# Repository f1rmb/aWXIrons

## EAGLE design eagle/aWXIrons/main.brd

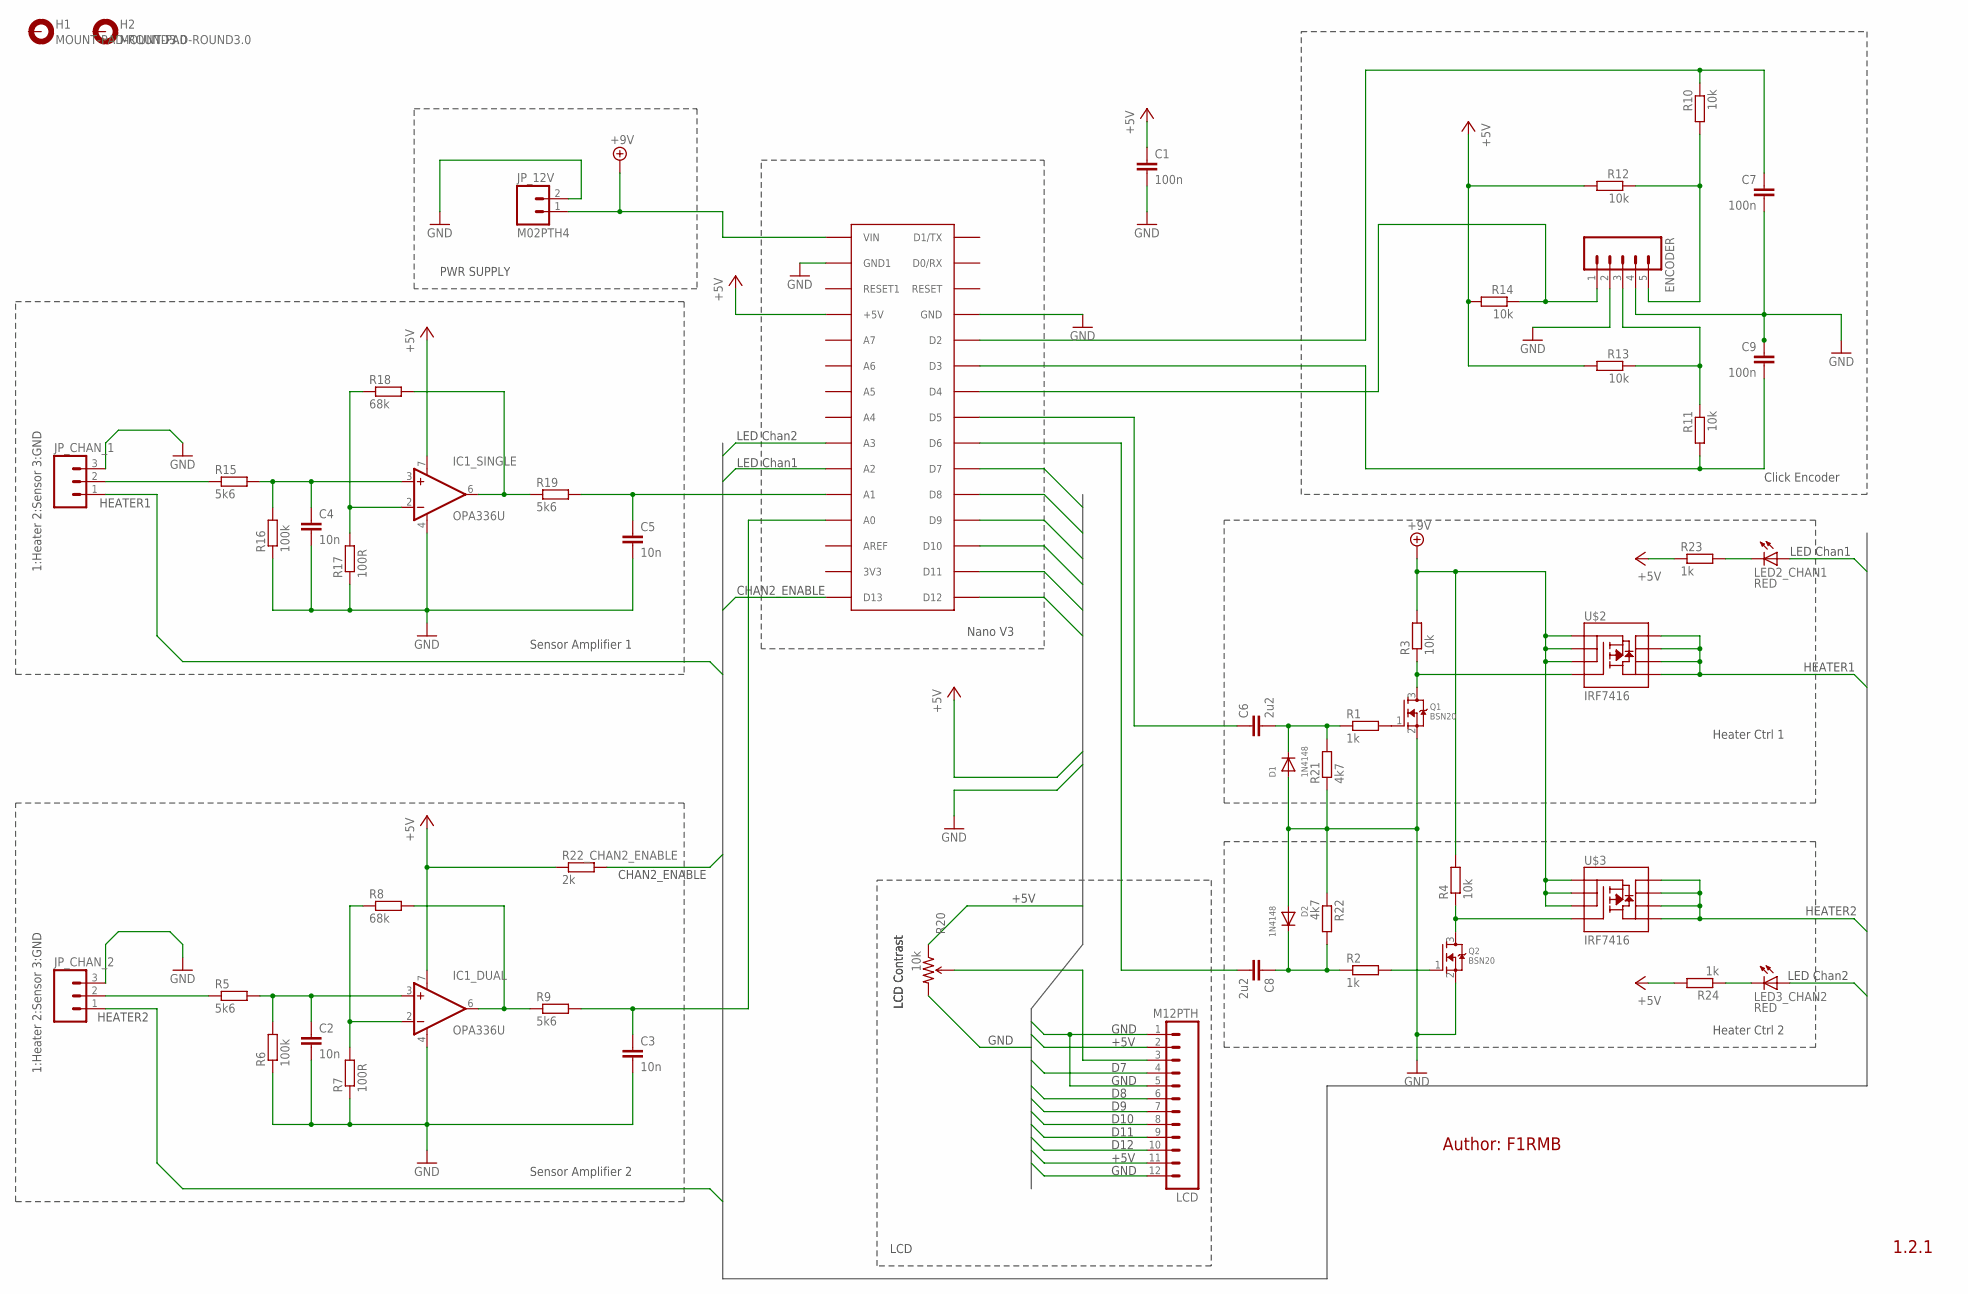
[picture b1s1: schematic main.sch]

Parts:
C1, C7, C9: 100n; C0805
C2, C3, C4, C5: 10n; C0805
C6, C8: 2u2; C0805
D1, D2: 1N4148; SOD-123
ENCODER: M05PTH; 1X05
H1, H2: MOUNT-PAD-ROUND3.0; 3,0-PAD
IC1_DUAL, IC1_SINGLE: OPA336U; SO08
JP_12V: M02PTH4; 1X02_XTRA_BIG
JP_CHAN_1, JP_CHAN_2: M03SCREW; SCREWTERMINAL-3.5MM-3
LCD: M12PTH; 1X12
LED2_CHAN1, LED3_CHAN2: RED; LED3MM
Q1, Q2: BSN20; SOT23
R1, R2, R23, R24: 1k; R0805
R3, R4, R10, R11, R12, R13, R14: 10k; R0805
R5, R9, R15, R19: 5k6; R0805
R6, R16: 100k; R0805
R7, R17: 100R; R0805
R8, R18: 68k; R0805
R20: 10k; 3362U-2
R21, R22: 4k7; R0805
R22_CHAN2_ENABLE: 2k; R0805
U$1: ARDUINONANO; PDIP-32
U$2, U$3: IRF7416; SO08

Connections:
+5V: C1.1, IC1_DUAL.7 (V+), IC1_SINGLE.7 (V+), LCD.2, LCD.11, R12.2, R13.2, R14.2, R20.1 (CCW), R22_CHAN2_ENABLE.1, R23.1, R24.2, U$1.+5V
+9V: JP_12V.1, R3.2, R4.2, U$1.VIN, U$2.1 (S), U$2.2 (S), U$2.3 (S), U$3.1 (S), U$3.2 (S), U$3.3 (S)
DB4: LCD.7, U$1.D9
DB5: LCD.8, U$1.D10
DB6: LCD.9, U$1.D11
DB7: LCD.10, U$1.D12
E: LCD.6, U$1.D8
ENABLECHAN2: R22_CHAN2_ENABLE.2, U$1.D13
GND: C1.2, C2.2, C3.2, C4.2, C5.2, C7.2, C9.1, D1.A, D2.A, ENCODER.2, ENCODER.4, IC1_DUAL.4 (V-), IC1_SINGLE.4 (V-), JP_12V.2, JP_CHAN_1.3, JP_CHAN_2.3, LCD.1, LCD.5, LCD.12, Q1.2 (S), Q2.2 (S), R6.1, R7.1, R16.1, R17.1, R20.3 (CW), R21.1, R22.1, U$1.GND, U$1.GND1
HEATCHAN1: LED2_CHAN1.A, U$1.A2
HEATCHAN2: LED3_CHAN2.A, U$1.A3
HEATER1: JP_CHAN_1.1, U$2.5 (D), U$2.6 (D), U$2.7 (D), U$2.8 (D)
HEATER2: JP_CHAN_2.1, U$3.5 (D), U$3.6 (D), U$3.7 (D), U$3.8 (D)
unnamed: Q1.3 (D), R3.1, U$2.4 (G)
unnamed: Q2.3 (D), R4.1, U$3.4 (G)
unnamed: JP_CHAN_2.2, R5.1
unnamed: C2.1, IC1_DUAL.3 (+IN), R5.2, R6.2
unnamed: IC1_DUAL.2 (-IN), R7.2, R8.1
unnamed: C7.1, R10.1, U$1.D2
unnamed: IC1_DUAL.6 (OUT), R8.2, R9.1
unnamed: JP_CHAN_1.2, R15.1
unnamed: C4.1, IC1_SINGLE.3 (+IN), R15.2, R16.2
unnamed: C6.1, U$1.D5
unnamed: C8.2, U$1.D6
unnamed: Q1.1 (G), R1.2
unnamed: Q2.1 (G), R2.2
unnamed: C3.1, R9.2, U$1.A0
unnamed: ENCODER.5, R10.2, R12.1
unnamed: LCD.3, R20.2 (WIPER)
unnamed: C6.2, D1.C, R1.1, R21.2
unnamed: ENCODER.3, R11.1, R13.1
unnamed: C9.2, R11.2, U$1.D3
unnamed: IC1_SINGLE.2 (-IN), R17.2, R18.1
unnamed: IC1_SINGLE.6 (OUT), R18.2, R19.1
unnamed: ENCODER.1, R14.1, U$1.D4
unnamed: C5.1, R19.2, U$1.A1
unnamed: C8.1, D2.C, R2.1, R22.2
unnamed: LED2_CHAN1.K (C), R23.2
unnamed: LED3_CHAN2.K (C), R24.1
RS: LCD.4, U$1.D7

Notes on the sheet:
1:Heater 2:Sensor 3:GND
PWR SUPPLY
LCD
Nano V3
Click Encoder
Sensor Amplifier 1
Sensor Amplifier 2
Heater Ctrl 1
Heater Ctrl 2
LED Chan1
LED Chan2
LCD Contrast
1.2.1
Author: F1RMB
CHAN2_ENABLE
+5V
GND
D10
D11
D12
HEATER1
HEATER2

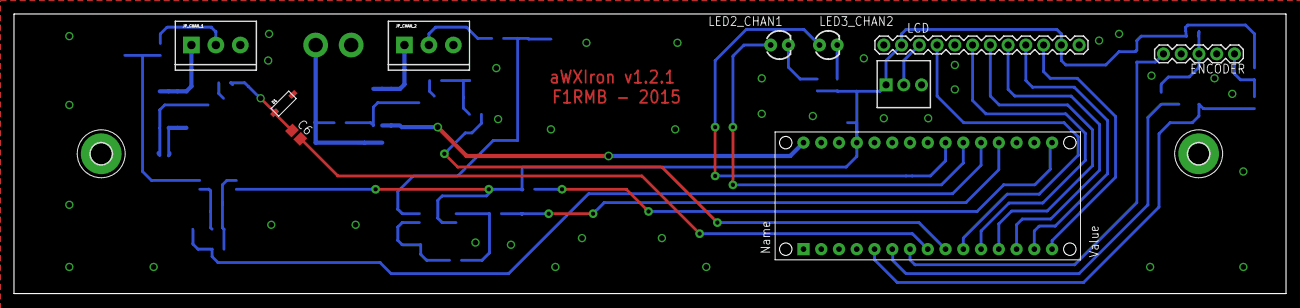
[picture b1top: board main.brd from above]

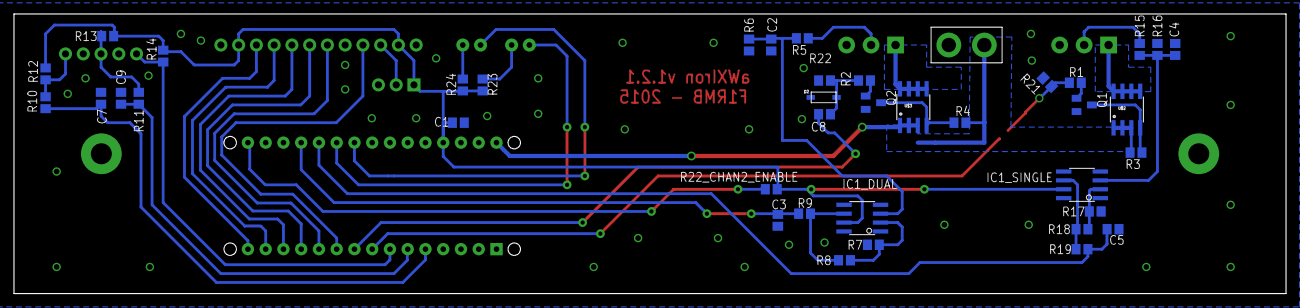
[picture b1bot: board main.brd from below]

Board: 2 copper layers, 182.0 x 40.0 mm, 52 parts (40 on the bottom side), 40 nets.

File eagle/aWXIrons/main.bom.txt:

Partlist exported from /home/daniel/eagle/Projects/aWXIrons/main.sch at 11/04/15 07:46

Assembly variant: 

Qty Value              Device                     Parts                          
2                      M03SCREW                   JP_CHAN_1, JP_CHAN_2           
1                      M05PTH                     ENCODER                        
2   1N4148             DIODESOD-123               D1, D2                         
4   1k                 R-EU_R0805                 R1, R2, R23, R24               
1   2k                 R-EU_R0805                 R22_CHAN2_ENABLE               
2   2u2                C-EUC0805                  C6, C8                         
2   4k7                R-EU_R0805                 R21, R22                       
4   5k6                R-EU_R0805                 R5, R9, R15, R19               
7   10k                R-EU_R0805                 R3, R4, R10, R11, R12, R13, R14
1   10k                TRIMPOT3362U-2             R20                            
4   10n                C-EUC0805                  C2, C3, C4, C5                 
2   68k                R-EU_R0805                 R8, R18                        
2   100R               R-EU_R0805                 R7, R17                        
2   100k               R-EU_R0805                 R6, R16                        
3   100n               C-EUC0805                  C1, C7, C9                     
1   ARDUINONANO        ARDUINONANO                U$1                            
2   BSN20              MOSFET-NREFLOW             Q1, Q2                         
2   IRF7416            MOSFET-PCHANNEL-SOIC8SOIC8 U$2, U$3                       
1   M02PTH4            M02PTH4                    JP_12V                         
1   M12PTH             M12PTH                     LCD                            
2   MOUNT-PAD-ROUND3.0 MOUNT-PAD-ROUND3.0         H1, H2                         
2   OPA336U            OPA336U                    IC1_DUAL, IC1_SINGLE           
2   RED                LED3MM                     LED2_CHAN1, LED3_CHAN2

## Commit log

2015-03-29 First Import.
2015-03-31 Finalize Makefile. Update doc (unfinished). Turn both channels PWM off while reading ADC. Add plugged tip detection (display shows '---' when unplugged). In joined channels mode, temperature display 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
2015-04-05 Finalize documentation. Fix calibration process.
2015-04-05 Added tag RELEASE-1.2_02042015 for changeset efbd99d3a2c3
2015-04-05 Prepare to publish on GitHub.
2015-04-11 Update PDFs
2015-04-13 - Displayed temperature is averaged. - Fix documentation (F6AZZ). - Bump version, update user manual.
2015-04-13 Revert "- Displayed temperature is averaged."
    This reverts commit 4ef88245852de1e1e4a668eb0dcc3ed734a76e18.
2015-04-13 - Displayed temperature is now averaged. - Fix documentation (F6AZZ). - Bump version, update user manual. - New release.
2015-04-13 Change +12V to +9V in schematic and PCBs. Update PDFs.
2015-04-13 Update doc version.
2016-03-10 Fix small if statement error (not critical). Bump version number. New HEX file.
2017-01-29 Fix averaging class, stupid me... Bump version.
2017-01-29 :CAL:DUMP displays EEPROM calibration values. Update copyright year. More cleanup.
2017-01-30 Reintroduce averaging made of double values. Use and fix usage of strcmp_P and snprintf_P. Update doc. Release.
2017-01-30 Forgot the HEX file...
2017-08-21 Make it compile on 'standard' arduino install (in /opt/arduino).

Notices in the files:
parts and their libraries:
SparkFun-Electromechanical: Licensing: Creative Commons ShareAlike 4.0 International - https://creativecommons.org/licenses/by-sa/4.0
